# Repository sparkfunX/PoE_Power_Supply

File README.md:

SparkFun PoE to USB Power Supply
===========================================================

[*SparkFun PoE to USB Power Supply (SPX-18709)*](https://www.sparkfun.com/products/18709)

It can be difficult to get a wall-wart where you need it. The promise of PoE (power over ethernet) is great, but what if your device doesn't use ethernet? Perhaps you could mess with power injectors, but what if you've already got PoE available on your network? The PoE to USB Power Supply is like a USB wall wart for PoE. Get a PoE hub, run ethernet wherever you need it, plug the PoE to USB Power Supply in and you'll have 5V at 1A via a USB A connector.

The onboard PoE module supports 36V to 57V DC input and provides up to 1.8A (9W) output. While the module claims 1.8A, we've pushed it to 1.5A before the module hit 75C and the output began to sag below 4.5V. The PoE to USB Power Supply has 1.5KV isolation, thermal cut off, and short circuit protection. The PoE module requires a 100mA load at all times so the PoE Power Supply includes a 50 Ohm resistor to constantly load the module with 100mA. There's a cuttable jumper to remove this load if needed. At a 1A load we measured a low 20mVPP ripple at 200kHz.

Who doesn't need 3.3V as well? In addition to the 5V provided via USB we've added a 3.3V 600mA regulator as well that can be connected via PTH solder connections. This is handy for systems running directly at 3.3V.

Repository Contents
-------------------

* **/Hardware** - Eagle files

License Information
-------------------

This product is _**open source**_! 

Various bits of the code have different licenses applied. Anything SparkFun wrote is beerware; if you see me (or any other SparkFun employee) at the local, and you've found our code helpful, please buy us a round!

Please use, reuse, and modify these files as you see fit. Please maintain attribution to SparkFun Electronics and release anything derivative under the same license.

Distributed as-is; no warranty is given.

- Your friends at SparkFun.

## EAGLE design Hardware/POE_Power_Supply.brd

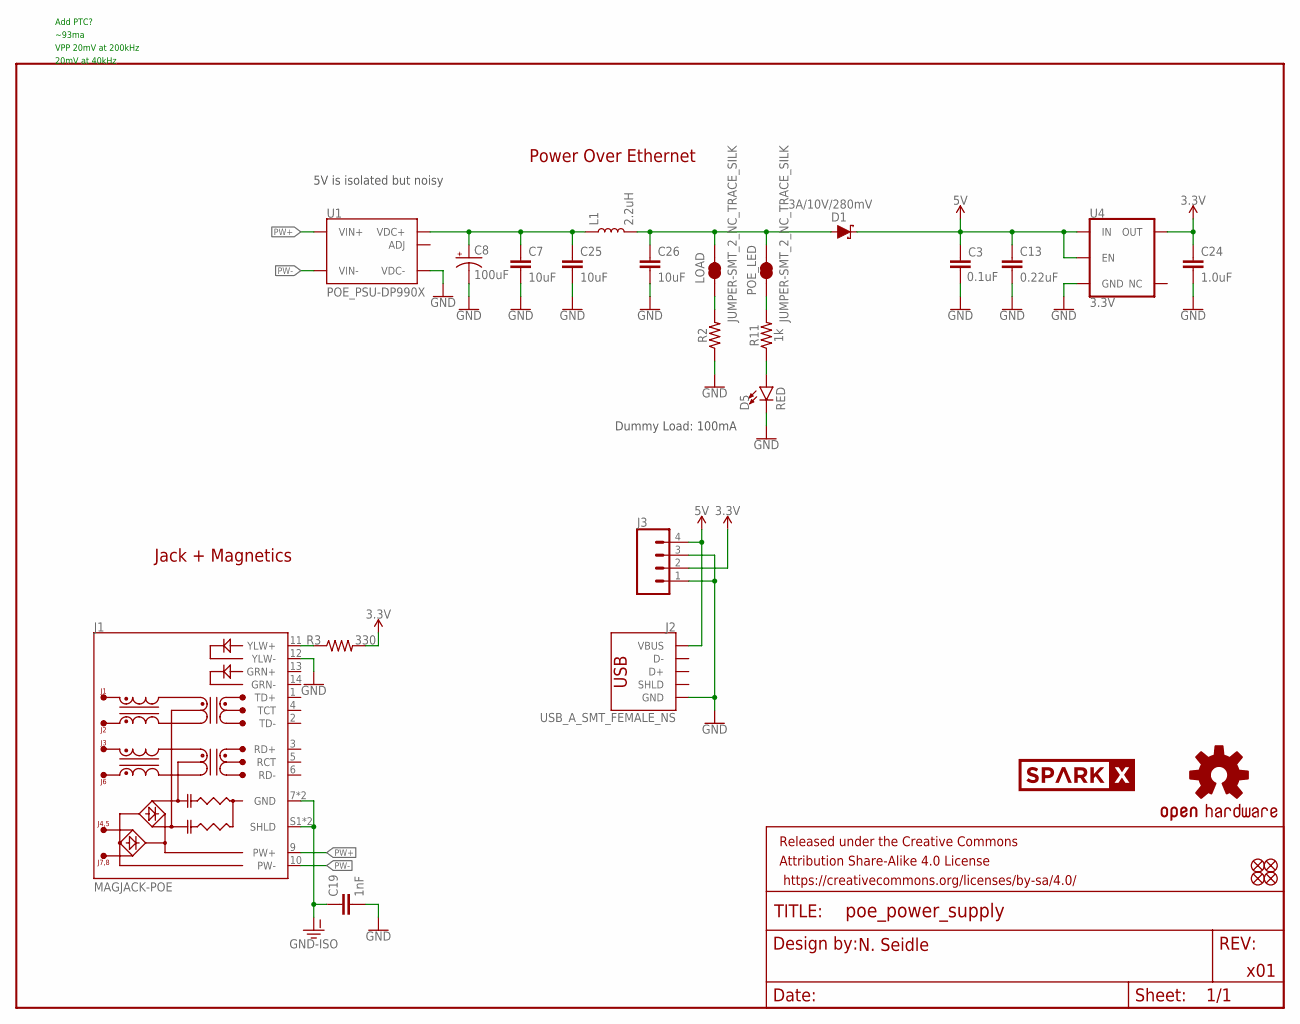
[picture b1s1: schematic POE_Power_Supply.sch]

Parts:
C3: 0.1uF; 0603
C7, C25, C26: 10uF; 0805
C8: 100uF; PANASONIC_D
C13: 0.22uF; 0603
C19: 1nF; 1206
C24: 1.0uF; 0603
D1: 3A/10V/280mV; SOD-323
D5: RED; LED-0603
FD1, FD2, FD3, FD4: FIDUCIALUFIDUCIAL; FIDUCIAL-MICRO
FRAME1: FRAME-LETTER; CREATIVE_COMMONS
J1: MAGJACK-POE; MAGJACK-SYM_LED
J2: USB_A_SMT_FEMALE_NS; USB-A-S-NOSILK-FEMALE
J3: CONN_041X04_NO_SILK; 1X04_NO_SILK
L1: 2.2uH; 0805-WIDE
LOAD: JUMPER-SMT_2_NC_TRACE_SILK; SMT-JUMPER_2_NC_TRACE_SILK
LOGO3: OSHW-LOGOMINI; OSHW-LOGO-MINI
POE_LED: JUMPER-SMT_2_NC_TRACE_SILK; SMT-JUMPER_2_NC_TRACE_SILK
R2: 49.9OHM-1206-1/2W-1%; 1206
R3: 330; 0603
R11: 1k; 0603
U1: POE_PSU-DP990X; DP990X
U4: 3.3V; SOT23-5
U$7: SPARKX-LOGO4; SPARKX-MEDIUM

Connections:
3.3V: C24.1, J3.2, R3.2, U4.5 (OUT)
5V: C3.1, C13.1, D1.C, J2.VBUS, J3.4, U4.1 (IN), U4.3 (EN)
5V_FILTER: C26.1, D1.A, L1.2, LOAD.2, POE_LED.2
5V_RAW: C7.1, C8.+, C25.1, L1.1, U1.1 (VDC+), U1.2 (VDC+)
GND: C3.2, C7.2, C8.-, C13.2, C19.2, C24.2, C25.2, C26.2, D5.C, J1.12 (YLW-), J2.GND, J3.1, J3.3, R2.1, U1.3 (VDC-), U4.2 (GND)
GND-ISO: C19.1, J1.7 (GND), J1.8 (GND), J1.S1 (SHLD), J1.S2 (SHLD)
unnamed: D5.A, R11.1
unnamed: POE_LED.1, R11.2
unnamed: LOAD.1, R2.2
unnamed: J1.11 (YLW+), R3.1
PW+: J1.9 (PW+), U1.5 (VIN+), U1.6 (VIN+)
PW-: J1.10 (PW-), U1.7 (VIN-), U1.8 (VIN-)

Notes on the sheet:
5V is isolated but noisy
x01
Jack + Magnetics
N. Seidle
Power Over Ethernet
Dummy Load: 100mA
Add PTC?
~93ma
VPP 20mV at 200kHz
20mV at 40kHz

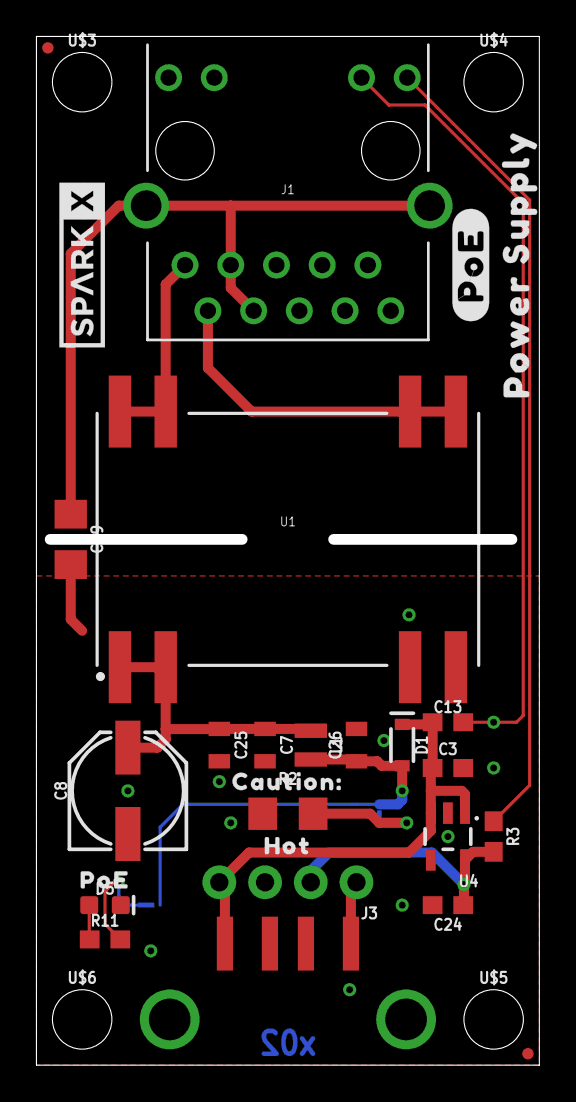
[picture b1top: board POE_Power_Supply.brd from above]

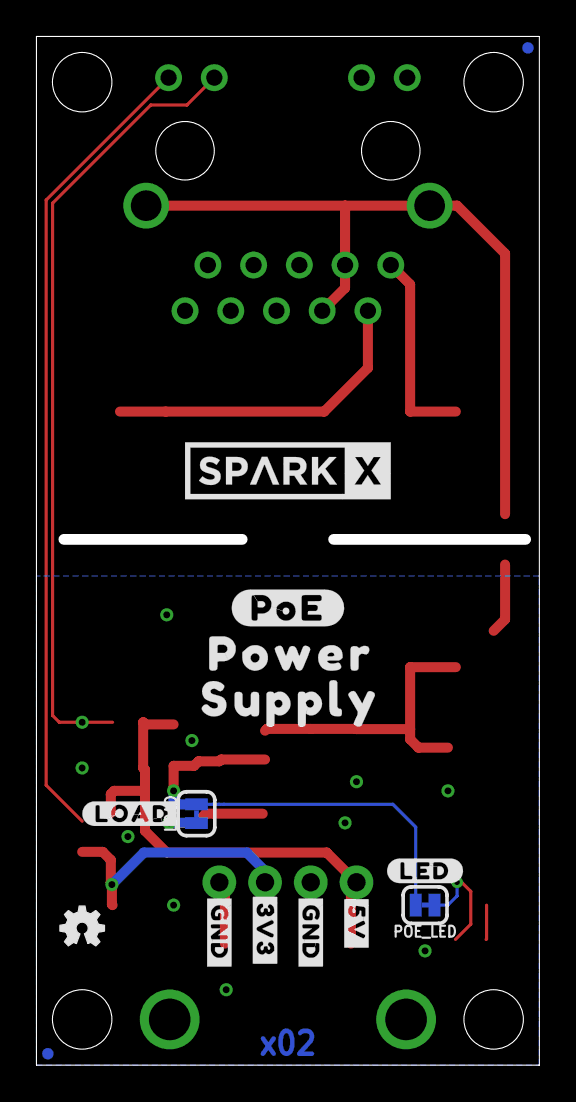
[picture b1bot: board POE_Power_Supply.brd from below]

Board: 2 copper layers, 27.4 x 56.6 mm, 48 parts (15 on the bottom side), 12 nets.

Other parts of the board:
U$1, U$18: #POE#0
U$3, U$4, U$5, U$6: STAND-OFF
U$8: #LED#0
U$9: #LOAD#0
U$10: #3V3#0
U$11: #5V#2
U$12, U$13: #GND#1
U$14: CAUTION#0
U$15: HOT1
U$16: POE0
U$17: POWER_0
U$19: SPARKX-LOGO4; SPARKX-LARGE
U$20: POWER0
U$21: SUPPLY1
U$22: SUPPLY_1

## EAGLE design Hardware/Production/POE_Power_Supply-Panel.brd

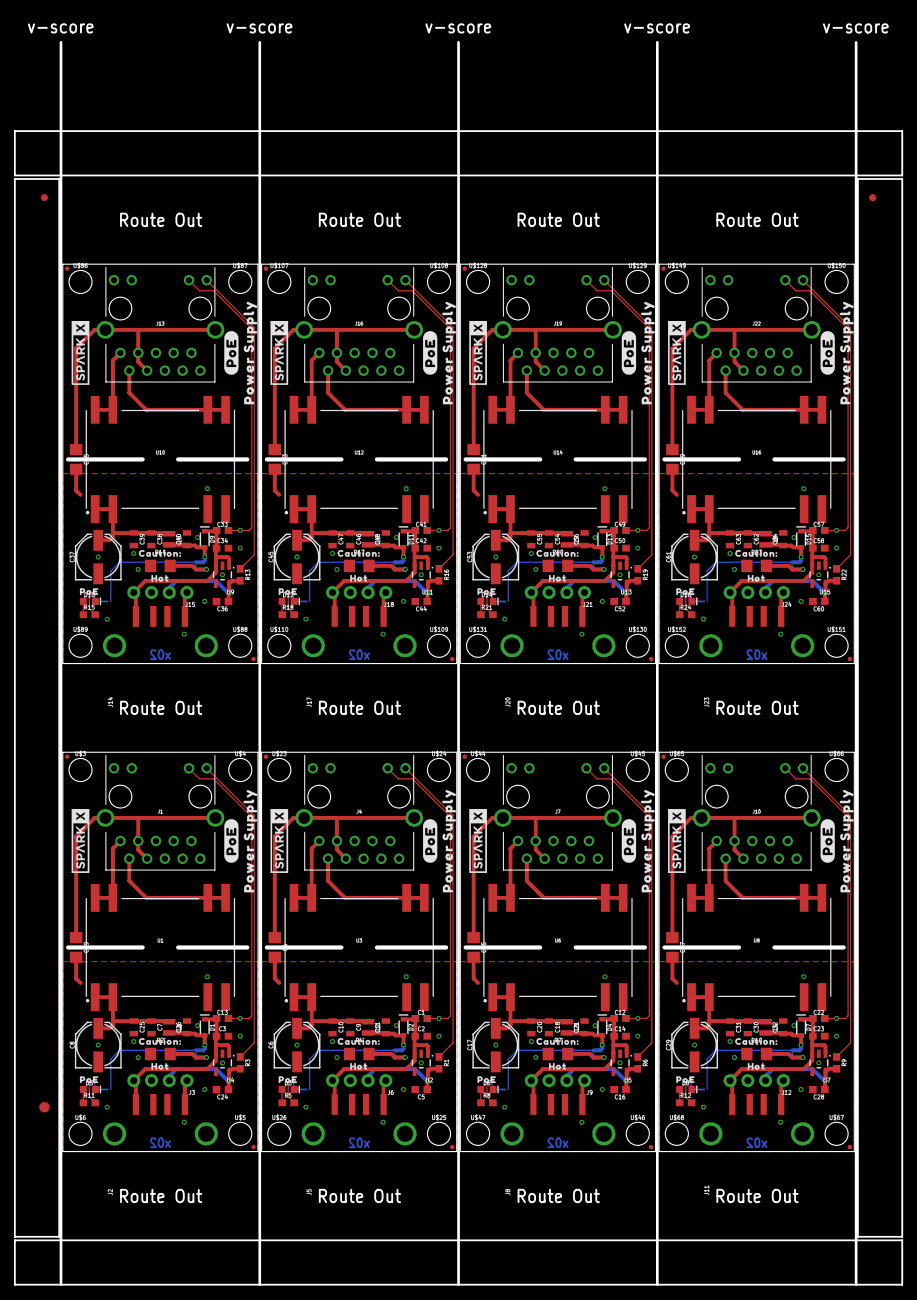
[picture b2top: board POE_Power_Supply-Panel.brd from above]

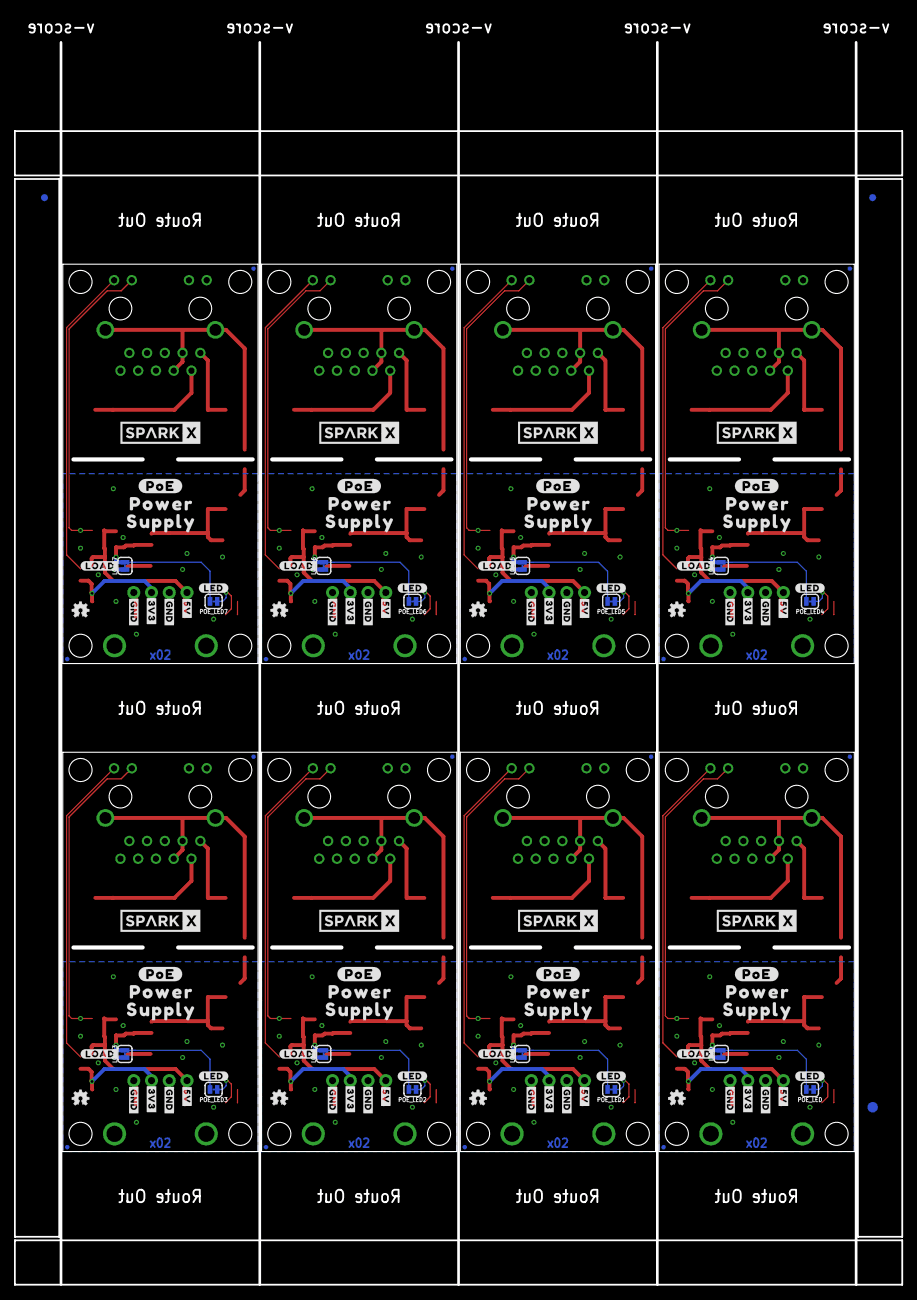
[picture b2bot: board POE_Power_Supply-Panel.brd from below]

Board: 2 copper layers, 126.7 x 181.5 mm, 382 parts (123 on the bottom side), 96 nets.

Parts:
C1, C12, C13, C22, C33, C41, C49, C57: 0.22uF; 0603
C2, C3, C14, C23, C34, C42, C50, C58: 0.1uF; 0603
C4, C15, C19, C27, C35, C43, C51, C59: 1nF; 1206
C5, C16, C24, C28, C36, C44, C52, C60: 1.0uF; 0603
C6, C8, C17, C29, C37, C45, C53, C61: 100uF; PANASONIC_D
C7, C9, C10, C11, C18, C20, C21, C25, C26, C30, C31, C32, C38, C39, C40, C46, C47, C48, C54, C55, C56, C62, C63, C64: 10uF; 0805
D1, D2, D4, D7, D9, D11, D13, D15: 3A/10V/280mV; SOD-323
D3, D5, D6, D8, D10, D12, D14, D16: RED; LED-0603
E$1, E$2, E$3, E$4: FIDUCIAL-1X2
E$5, E$6: FIDUCIAL-1.5X3
FD1, FD2, FD3, FD4, FD5, FD6, FD7, FD8, FD9, FD10, FD11, FD12, FD13, FD14, FD15, FD16, FD17, FD18, FD19, FD20, FD21, FD22, FD23, FD24, FD25, FD26, FD27, FD28, FD29, FD30, FD31, FD32: FIDUCIALUFIDUCIAL; FIDUCIAL-MICRO
J1, J4, J7, J10, J13, J16, J19, J22: MAGJACK-POE; MAGJACK-SYM_LED
J2, J5, J8, J11, J14, J17, J20, J23: USB_A_SMT_FEMALE_NS; USB-A-S-NOSILK-FEMALE
J3, J6, J9, J12, J15, J18, J21, J24: 1X04_NO_SILK
L1, L2, L3, L4, L5, L6, L7, L8: 2.2uH; 0805-WIDE
LOAD, LOAD1, LOAD2, LOAD3, LOAD4, LOAD5, LOAD6, LOAD7: JUMPER-SMT_2_NC_TRACE_SILK; SMT-JUMPER_2_NC_TRACE_SILK
LOGO1, LOGO2, LOGO3, LOGO4, LOGO5, LOGO6, LOGO7, LOGO8: OSHW-LOGOMINI; OSHW-LOGO-MINI
POE_LED, POE_LED1, POE_LED2, POE_LED3, POE_LED4, POE_LED5, POE_LED6, POE_LED7: JUMPER-SMT_2_NC_TRACE_SILK; SMT-JUMPER_2_NC_TRACE_SILK
R1, R3, R6, R9, R13, R16, R19, R22: 330; 0603
R2, R4, R7, R10, R14, R17, R20, R23: 49.9OHM-1206-1/2W-1%; 1206
R5, R8, R11, R12, R15, R18, R21, R24: 1k; 0603
U1, U3, U6, U8, U10, U12, U14, U16: POE_PSU-DP990X; DP990X
U2, U4, U5, U7, U9, U11, U13, U15: 3.3V; SOT23-5
U$1, U$2, U$18, U$42, U$43, U$63, U$64, U$84, U$85, U$105, U$106, U$126, U$127, U$147, U$148, U$168: #POE#0
U$3, U$4, U$5, U$6, U$23, U$24, U$25, U$26, U$44, U$45, U$46, U$47, U$65, U$66, U$67, U$68, U$86, U$87, U$88, U$89, U$107, U$108, U$109, U$110, U$128, U$129, U$130, U$131, U$149, U$150, U$151, U$152: STAND-OFF
U$7, U$36, U$57, U$78, U$99, U$120, U$141, U$162: SPARKX-LOGO4; SPARKX-MEDIUM
U$8, U$27, U$48, U$69, U$90, U$111, U$132, U$153: #LED#0
U$9, U$28, U$49, U$70, U$91, U$112, U$133, U$154: #LOAD#0
U$10, U$29, U$50, U$71, U$92, U$113, U$134, U$155: #3V3#0
U$11, U$30, U$51, U$72, U$93, U$114, U$135, U$156: #5V#2
U$12, U$13, U$31, U$32, U$52, U$53, U$73, U$74, U$94, U$95, U$115, U$116, U$136, U$137, U$157, U$158: #GND#1
U$14, U$33, U$54, U$75, U$96, U$117, U$138, U$159: CAUTION#0
U$15, U$34, U$55, U$76, U$97, U$118, U$139, U$160: HOT1
U$16, U$35, U$56, U$77, U$98, U$119, U$140, U$161: POE0
U$17, U$40, U$61, U$82, U$103, U$124, U$145, U$166: POWER_0
U$19, U$37, U$58, U$79, U$100, U$121, U$142, U$163: SPARKX-LOGO4; SPARKX-LARGE
U$20, U$38, U$59, U$80, U$101, U$122, U$143, U$164: POWER0
U$21, U$39, U$60, U$81, U$102, U$123, U$144, U$165: SUPPLY1
U$22, U$41, U$62, U$83, U$104, U$125, U$146, U$167: SUPPLY_1

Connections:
3.3V: C24.1, J3.2, R3.2, U4.5
3.3V1: C5.1, J6.2, R1.2, U2.5
3.3V2: C16.1, J9.2, R6.2, U5.5
3.3V3: C28.1, J12.2, R9.2, U7.5
3.3V4: C36.1, J15.2, R13.2, U9.5
3.3V5: C44.1, J18.2, R16.2, U11.5
3.3V6: C52.1, J21.2, R19.2, U13.5
3.3V7: C60.1, J24.2, R22.2, U15.5
5V: C3.1, C13.1, D1.C, J2.VBUS, J3.4, U4.1, U4.3
5V1: C1.1, C2.1, D2.C, J5.VBUS, J6.4, U2.1, U2.3
5V2: C12.1, C14.1, D4.C, J8.VBUS, J9.4, U5.1, U5.3
5V3: C22.1, C23.1, D7.C, J11.VBUS, J12.4, U7.1, U7.3
5V4: C33.1, C34.1, D9.C, J14.VBUS, J15.4, U9.1, U9.3
5V5: C41.1, C42.1, D11.C, J17.VBUS, J18.4, U11.1, U11.3
5V6: C49.1, C50.1, D13.C, J20.VBUS, J21.4, U13.1, U13.3
5V7: C57.1, C58.1, D15.C, J23.VBUS, J24.4, U15.1, U15.3
5V_FILTER: C26.1, D1.A, L1.2, LOAD.2, POE_LED.2
5V_FILTER1: C11.1, D2.A, L2.2, LOAD1.2, POE_LED1.2
5V_FILTER2: C21.1, D4.A, L3.2, LOAD2.2, POE_LED2.2
5V_FILTER3: C32.1, D7.A, L4.2, LOAD3.2, POE_LED3.2
5V_FILTER4: C40.1, D9.A, L5.2, LOAD4.2, POE_LED4.2
5V_FILTER5: C48.1, D11.A, L6.2, LOAD5.2, POE_LED5.2
5V_FILTER6: C56.1, D13.A, L7.2, LOAD6.2, POE_LED6.2
5V_FILTER7: C64.1, D15.A, L8.2, LOAD7.2, POE_LED7.2
5V_RAW: C7.1, C8.+, C25.1, L1.1, U1.1, U1.2
5V_RAW1: C6.+, C9.1, C10.1, L2.1, U3.1, U3.2
5V_RAW2: C17.+, C18.1, C20.1, L3.1, U6.1, U6.2
5V_RAW3: C29.+, C30.1, C31.1, L4.1, U8.1, U8.2
5V_RAW4: C37.+, C38.1, C39.1, L5.1, U10.1, U10.2
5V_RAW5: C45.+, C46.1, C47.1, L6.1, U12.1, U12.2
5V_RAW6: C53.+, C54.1, C55.1, L7.1, U14.1, U14.2
5V_RAW7: C61.+, C62.1, C63.1, L8.1, U16.1, U16.2
GND: C3.2, C7.2, C8.-, C13.2, C19.2, C24.2, C25.2, C26.2, D5.C, J1.12, J2.GND, J3.1, J3.3, R2.1, U1.3, U4.2
GND1: C1.2, C2.2, C4.2, C5.2, C6.-, C9.2, C10.2, C11.2, D3.C, J4.12, J5.GND, J6.1, J6.3, R4.1, U2.2, U3.3
GND2: C12.2, C14.2, C15.2, C16.2, C17.-, C18.2, C20.2, C21.2, D6.C, J7.12, J8.GND, J9.1, J9.3, R7.1, U5.2, U6.3
GND3: C22.2, C23.2, C27.2, C28.2, C29.-, C30.2, C31.2, C32.2, D8.C, J10.12, J11.GND, J12.1, J12.3, R10.1, U7.2, U8.3
GND4: C33.2, C34.2, C35.2, C36.2, C37.-, C38.2, C39.2, C40.2, D10.C, J13.12, J14.GND, J15.1, J15.3, R14.1, U9.2, U10.3
GND5: C41.2, C42.2, C43.2, C44.2, C45.-, C46.2, C47.2, C48.2, D12.C, J16.12, J17.GND, J18.1, J18.3, R17.1, U11.2, U12.3
GND6: C49.2, C50.2, C51.2, C52.2, C53.-, C54.2, C55.2, C56.2, D14.C, J19.12, J20.GND, J21.1, J21.3, R20.1, U13.2, U14.3
GND7: C57.2, C58.2, C59.2, C60.2, C61.-, C62.2, C63.2, C64.2, D16.C, J22.12, J23.GND, J24.1, J24.3, R23.1, U15.2, U16.3
GND-ISO: C19.1, J1.7, J1.8, J1.S1, J1.S2
GND-ISO1: C4.1, J4.7, J4.8, J4.S1, J4.S2
GND-ISO2: C15.1, J7.7, J7.8, J7.S1, J7.S2
GND-ISO3: C27.1, J10.7, J10.8, J10.S1, J10.S2
GND-ISO4: C35.1, J13.7, J13.8, J13.S1, J13.S2
GND-ISO5: C43.1, J16.7, J16.8, J16.S1, J16.S2
GND-ISO6: C51.1, J19.7, J19.8, J19.S1, J19.S2
GND-ISO7: C59.1, J22.7, J22.8, J22.S1, J22.S2
unnamed: J4.11, R1.1
unnamed: LOAD1.1, R4.2
unnamed: POE_LED1.1, R5.2
unnamed: D3.A, R5.1
unnamed: D5.A, R11.1
unnamed: POE_LED.1, R11.2
unnamed: J7.11, R6.1
unnamed: LOAD2.1, R7.2
unnamed: LOAD.1, R2.2
unnamed: J1.11, R3.1
unnamed: POE_LED2.1, R8.2
unnamed: D6.A, R8.1
unnamed: J10.11, R9.1
unnamed: LOAD3.1, R10.2
unnamed: POE_LED3.1, R12.2
unnamed: D8.A, R12.1
unnamed: J13.11, R13.1
unnamed: LOAD4.1, R14.2
unnamed: POE_LED4.1, R15.2
unnamed: D10.A, R15.1
unnamed: J16.11, R16.1
unnamed: LOAD5.1, R17.2
unnamed: POE_LED5.1, R18.2
unnamed: D12.A, R18.1
unnamed: J19.11, R19.1
unnamed: LOAD6.1, R20.2
unnamed: POE_LED6.1, R21.2
unnamed: D14.A, R21.1
unnamed: J22.11, R22.1
unnamed: LOAD7.1, R23.2
unnamed: POE_LED7.1, R24.2
unnamed: D16.A, R24.1
PW+: J1.9, U1.5, U1.6
PW+1: J4.9, U3.5, U3.6
PW+2: J7.9, U6.5, U6.6
PW+3: J10.9, U8.5, U8.6
PW+4: J13.9, U10.5, U10.6
PW+5: J16.9, U12.5, U12.6
PW+6: J19.9, U14.5, U14.6
PW+7: J22.9, U16.5, U16.6
PW-: J1.10, U1.7, U1.8
PW-1: J4.10, U3.7, U3.8
PW-2: J7.10, U6.7, U6.8
PW-3: J10.10, U8.7, U8.8
PW-4: J13.10, U10.7, U10.8
PW-5: J16.10, U12.7, U12.8
PW-6: J19.10, U14.7, U14.8
PW-7: J22.10, U16.7, U16.8

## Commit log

2021-10-27 Add silk labels. Remove backup files. Add ignore.
2021-10-27 Add dims.
2021-11-29 Update x02. Fix FP for load resistor.
2022-02-16 Add schematic

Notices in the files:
parts and their libraries:
SparkFun-Aesthetics: Licensing: Creative Commons ShareAlike 4.0 International - https://creativecommons.org/licenses/by-sa/4.0
SparkFun-Aesthetics: Released under the Creative Commons Attribution Share-Alike 4.0 License
SparkFun-Aesthetics: https://creativecommons.org/licenses/by-sa/4.0
